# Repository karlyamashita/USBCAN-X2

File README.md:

USBCAN-X2 dual CAN bus analyzer using a STM32G491CE.

The schematic and gerber files are open source.

### Description
I have been working on a [CAN Jammer](https://github.com/karlyamashita/CAN_Jammer_STM32F105RB) project and need a dual CAN bus analyzer that uses 1 STM32 microcontroller. I am finding it difficult to find a vendor that sells a dual CAN bus analyzer that uses an STM32 that is open source and does not read protect the STM32 at RDP level 2. Most vendors that i've contacted are using NXP or a Chinese brand microcontroller. 
<br><br>
Because of the difficulties of finding a dual CAN bus analyzer, I've decided to create this open source project. Since FDCAN is becoming more mainstream, I've decided to use the STM32G491CE with FDCAN controllers which meet the requirements. 

### PCB
The PBC was designed around the USBCAN-2A, matching the USB and screw terminal connector. I am hoping some Chinese manufacturer or someone local will start to manufacture this project to make readily available for purchase. Since the plastic case seems to be a dime a dozen, it will make it easier fo manufacturers to have a completely enclosed product without the need to tool for a new case, if I did create a different size PCB.

`USBCAN-2A`

### Firmware
The FW is being developed and will be open source.

### Software
CAN-X will support the USBCAN-X2 once the Firmware is done.

### Image
This is the 3D image of the USBCAN-X2

`USBCAN-X2`

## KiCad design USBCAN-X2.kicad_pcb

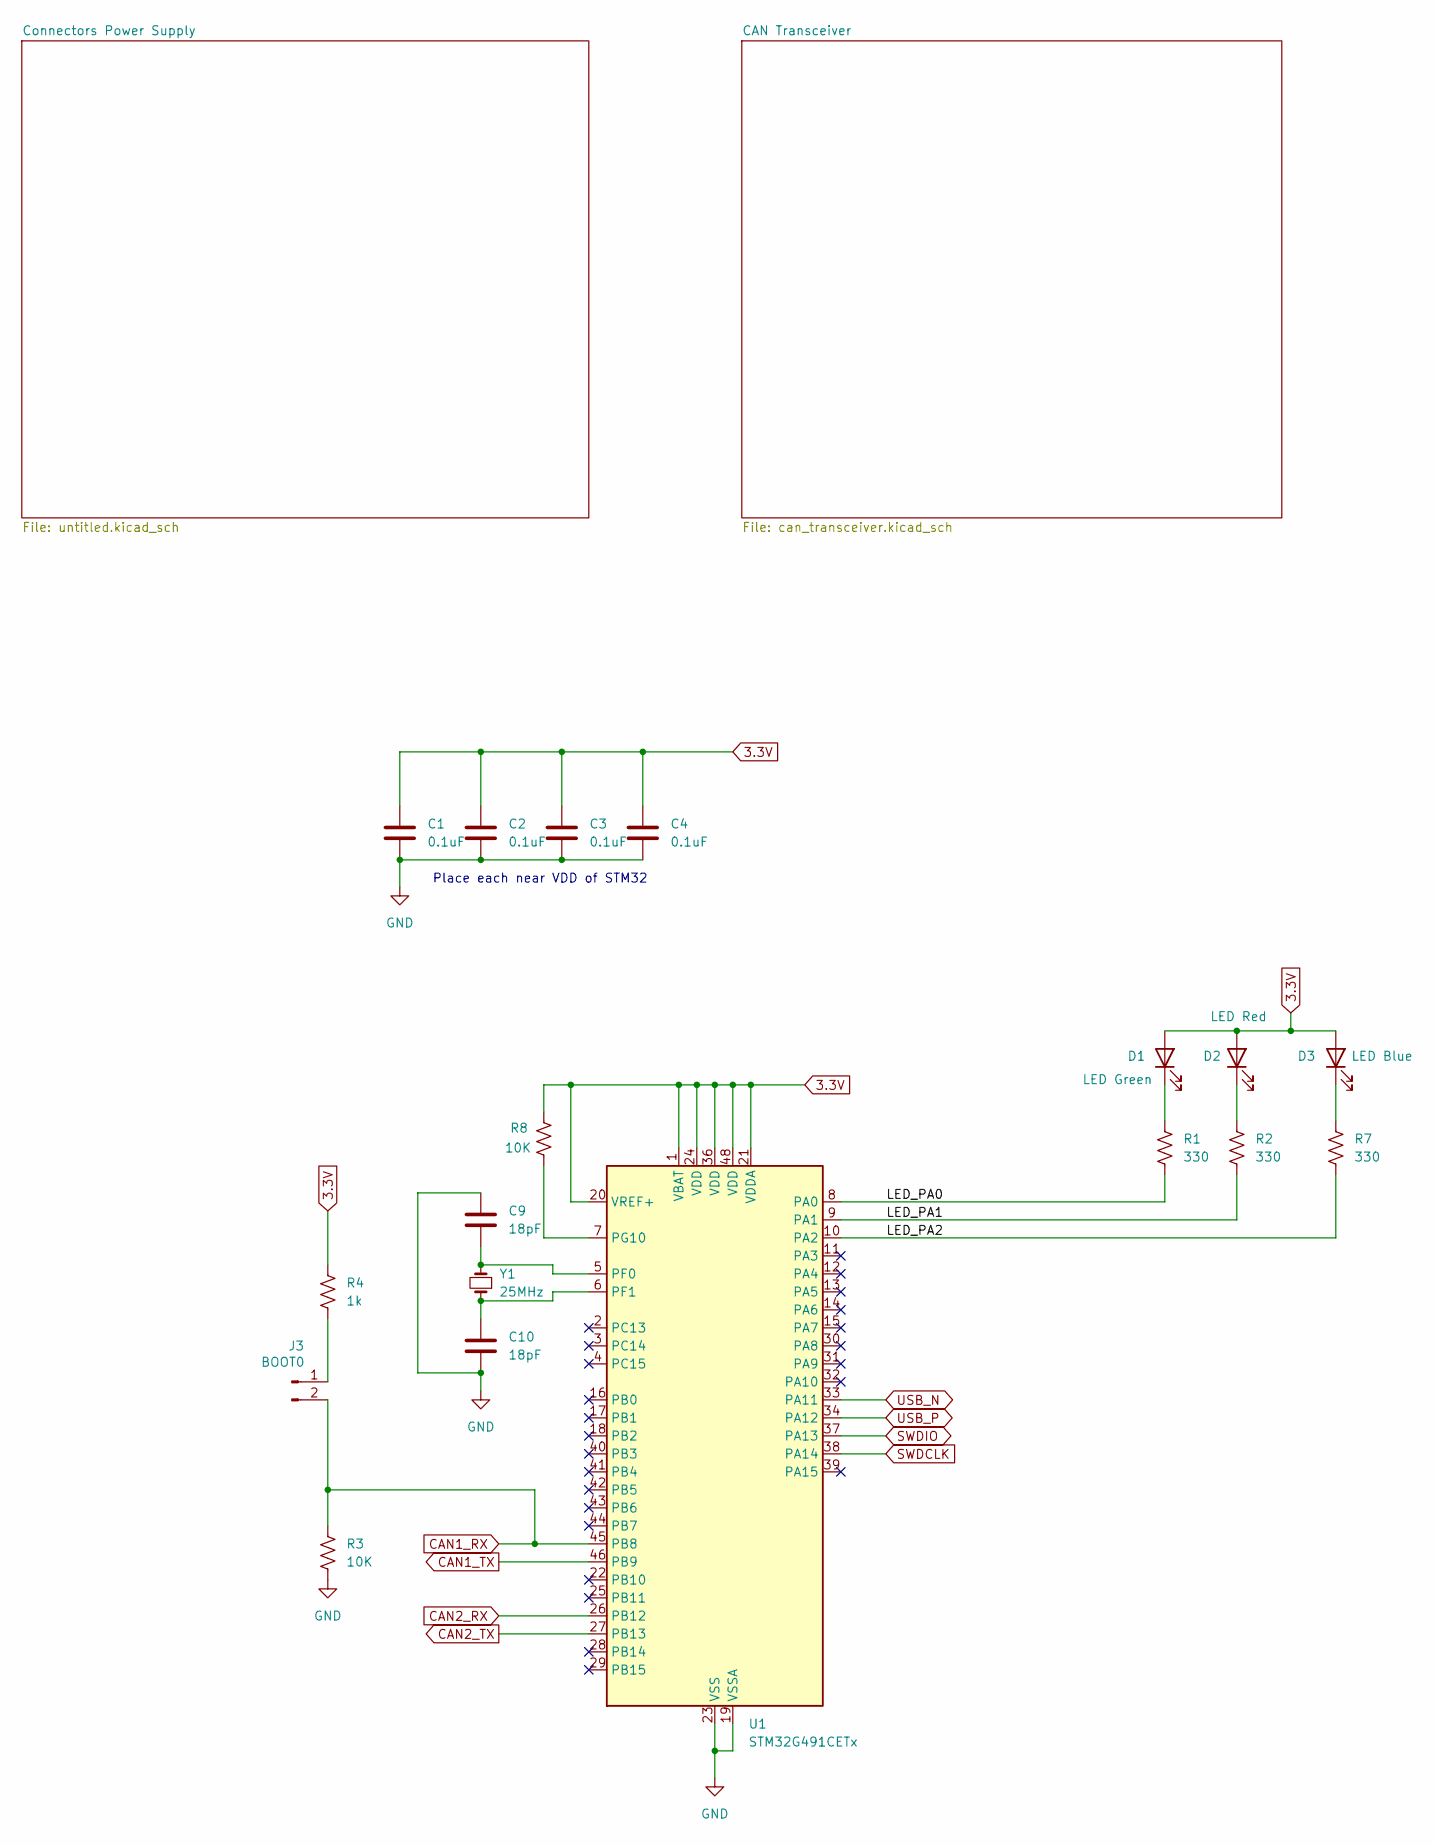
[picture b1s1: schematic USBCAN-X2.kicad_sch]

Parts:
C1, C2, C3, C4: 0.1uF; C_0603_1608Metric; Mouser 603-C0603ZRY5V9BB104
C9, C10: 18pF; C_0603_1608Metric; Mouser 791-RF18N180J500CT
D1: LED Red; LED_0603_1608Metric; Mouser 710-150060RS83000
D2: LED Green; LED_0603_1608Metric; Mouser 710-150060GS83000
D3: LED Blue; LED_0603_1608Metric; Mouser 710-150060BS83000
J3: BOOT0; PinHeader_1x02_P2.54mm_Vertical
R1, R2, R7: 330; R_0603_1608Metric; Mouser 774-73L2R33J
R3, R8: 10K; R_0603_1608Metric; Mouser 603-AC0603JR-7W10KL
R4: 1k; R_0603_1608Metric; Mouser 603-SR0603JR-071KL
U1: STM32G491CETx; LQFP-48_7x7mm_P0.5mm; Mouser 511-STM32G491CET6
Y1: 25MHz; Crystal_SMD_Abracon_ABM7-2Pin_6.0x3.5mm; Mouser 815-ABM725000MHZ4T

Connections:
3.3V: C1.1, C2.1, C3.1, C4.1, D1.2 (A), D2.2 (A), D3.2 (A), R4.1, R8.1, U1.1 (VBAT), U1.20 (VREF+), U1.21 (VDDA), U1.24 (VDD), U1.36 (VDD), U1.48 (VDD); also elsewhere on the board
/LED_PA0: R1.2, U1.8 (PA0)
/LED_PA1: R2.2, U1.9 (PA1)
/LED_PA2: R7.2, U1.10 (PA2)
CAN1_RX: J3.2, R3.1, U1.45 (PB8); also elsewhere on the board
CAN1_TX: U1.46 (PB9); also elsewhere on the board
CAN2_RX: U1.26 (PB12); also elsewhere on the board
CAN2_TX: U1.27 (PB13); also elsewhere on the board
GND: C1.2, C2.2, C3.2, C4.2, C9.1, C10.2, R3.2, U1.19 (VSSA), U1.23 (VSS), U1.35 (VSS), U1.47 (VSS); also elsewhere on the board
unnamed: D1.1 (K), R1.1
unnamed: D2.1 (K), R2.1
unnamed: D3.1 (K), R7.1
unnamed: J3.1, R4.2
unnamed: C9.2, U1.5 (PF0), Y1.2
unnamed: C10.1, U1.6 (PF1), Y1.1
unnamed: R8.2, U1.7 (PG10)
SWDCLK: U1.38 (PA14); also elsewhere on the board
SWDIO: U1.37 (PA13); also elsewhere on the board
USB_N: U1.33 (PA11); also elsewhere on the board
USB_P: U1.34 (PA12); also elsewhere on the board

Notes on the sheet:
Place each near VDD of STM32

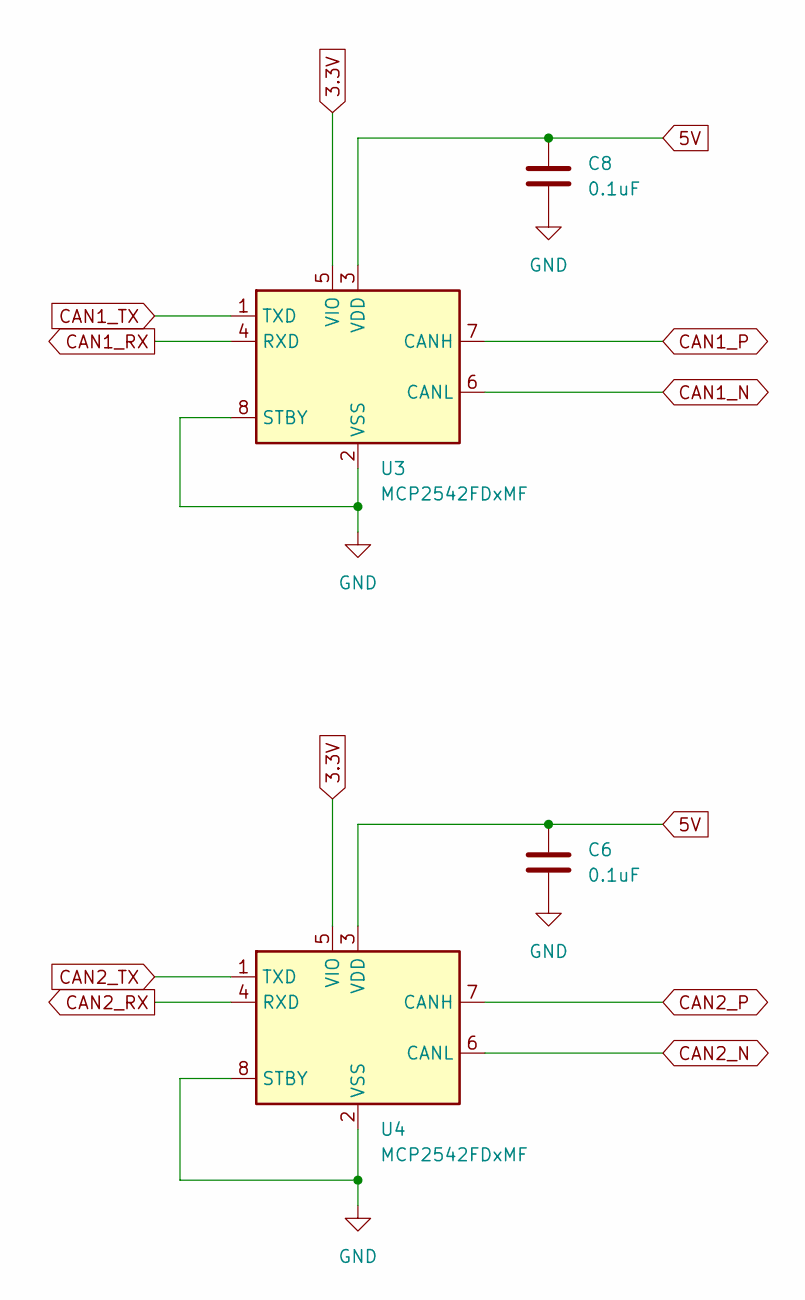
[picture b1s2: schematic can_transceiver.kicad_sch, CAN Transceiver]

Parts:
C6, C8: 0.1uF; C_0603_1608Metric; Mouser 603-C0603ZRY5V9BB104
U3, U4: MCP2542FDxMF; SOIC-8-1EP_3.9x4.9mm_P1.27mm_EP2.29x3mm; Mouser 579-MCP2542FD-E/SN

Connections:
3.3V: U3.5 (VIO), U4.5 (VIO); also elsewhere on the board
5V: C6.1, C8.1, U3.3 (VDD), U4.3 (VDD); also elsewhere on the board
CAN1_N: U3.6 (CANL); also elsewhere on the board
CAN1_P: U3.7 (CANH); also elsewhere on the board
CAN1_RX: U3.4 (RXD); also elsewhere on the board
CAN1_TX: U3.1 (TXD); also elsewhere on the board
CAN2_N: U4.6 (CANL); also elsewhere on the board
CAN2_P: U4.7 (CANH); also elsewhere on the board
CAN2_RX: U4.4 (RXD); also elsewhere on the board
CAN2_TX: U4.1 (TXD); also elsewhere on the board
GND: C6.2, C8.2, U3.2 (VSS), U3.8 (STBY), U3.9 (VSS), U4.2 (VSS), U4.8 (STBY), U4.9 (VSS); also elsewhere on the board

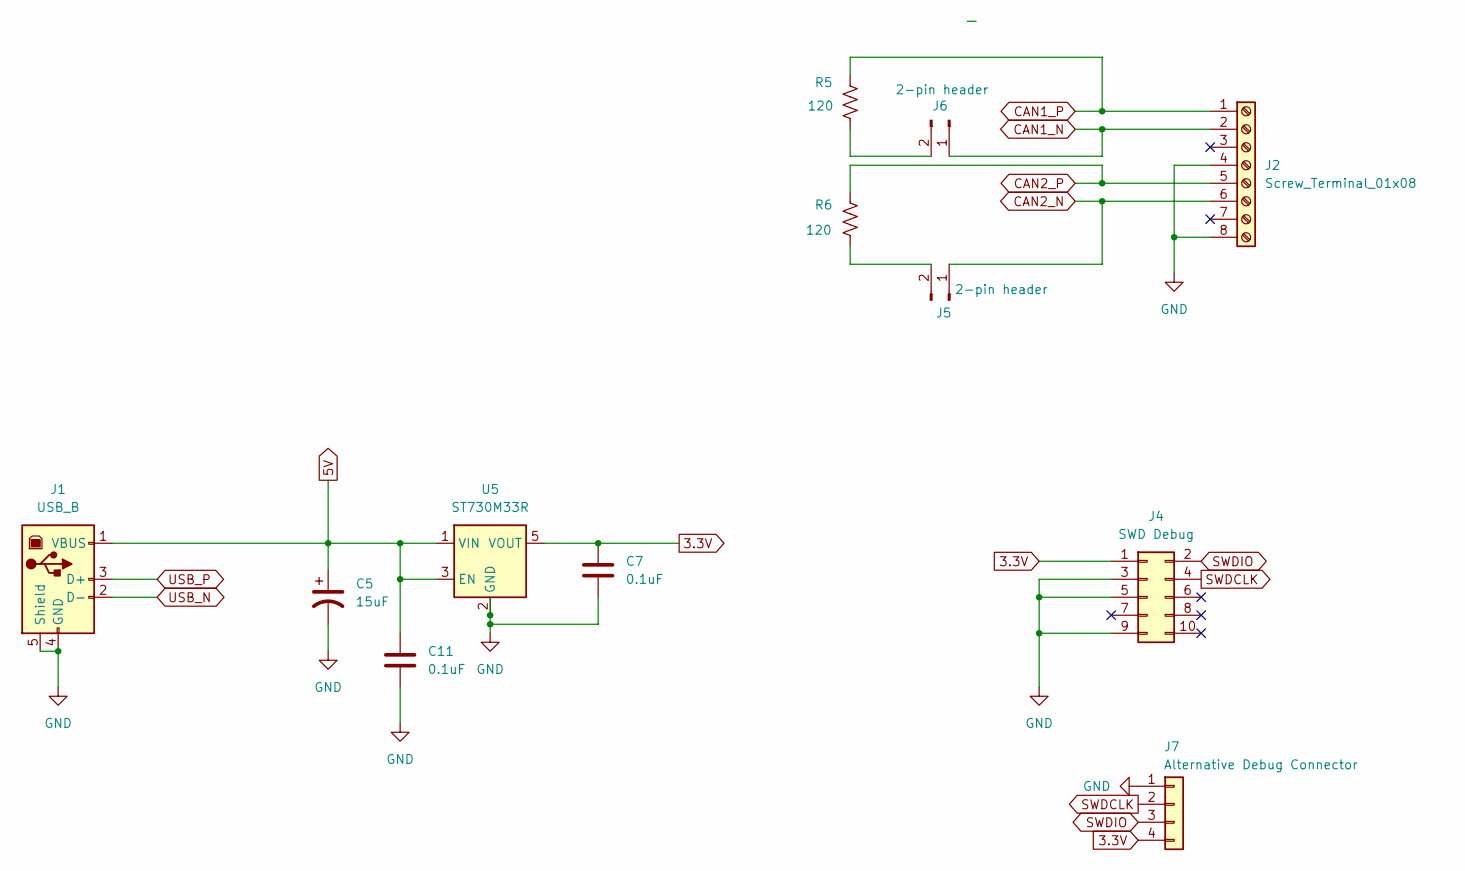
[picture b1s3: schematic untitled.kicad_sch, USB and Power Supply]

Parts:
C5: 15uF; C_Elec_4x5.4; Mouser 667-10SVP15M
C7, C11: 0.1uF; C_0603_1608Metric; Mouser 603-C0603ZRY5V9BB104
J1: USB_B; USB_B_Lumberg_2411_02_Horizontal; Mouser 523-UE27-BC54-100
J2: Screw_Terminal_01x08; Amphenol Anytek OQ0812510000G; Mouser 649-220110-C081A01LF
J4: SWD Debug; CON10_2X5_DUK_FTSH_SAI-M; Mouser 200-FTSH10501LDVKP
J5, J6: 2-pin header; PinHeader_1x02_P2.54mm_Vertical
J7: Alternative Debug Connector; PinHeader_1x04_P2.54mm_Vertical
R5, R6: 120; R_0603_1608Metric; Mouser 603-RC0603FR-13120RL
U5: ST730M33R; SOT-23-5; Mouser ST730M33R

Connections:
3.3V: C7.1, J4.1, J7.4, U5.5 (VOUT); also elsewhere on the board
5V: C5.1, C11.1, J1.1 (VBUS), U5.1 (VIN), U5.3 (EN); also elsewhere on the board
CAN1_N: J2.2, J6.1; also elsewhere on the board
CAN1_P: J2.1, R5.1; also elsewhere on the board
CAN2_N: J2.6, J5.1; also elsewhere on the board
CAN2_P: J2.5, R6.1; also elsewhere on the board
GND: C5.2, C7.2, C11.2, J1.4 (GND), J1.5 (Shield), J2.4, J2.8, J4.3, J4.5, J4.9, J7.1, U5.2 (GND); also elsewhere on the board
unnamed: J5.2, R6.2
unnamed: J6.2, R5.2
SWDCLK: J4.4, J7.2; also elsewhere on the board
SWDIO: J4.2, J7.3; also elsewhere on the board
USB_N: J1.2 (D-); also elsewhere on the board
USB_P: J1.3 (D+); also elsewhere on the board

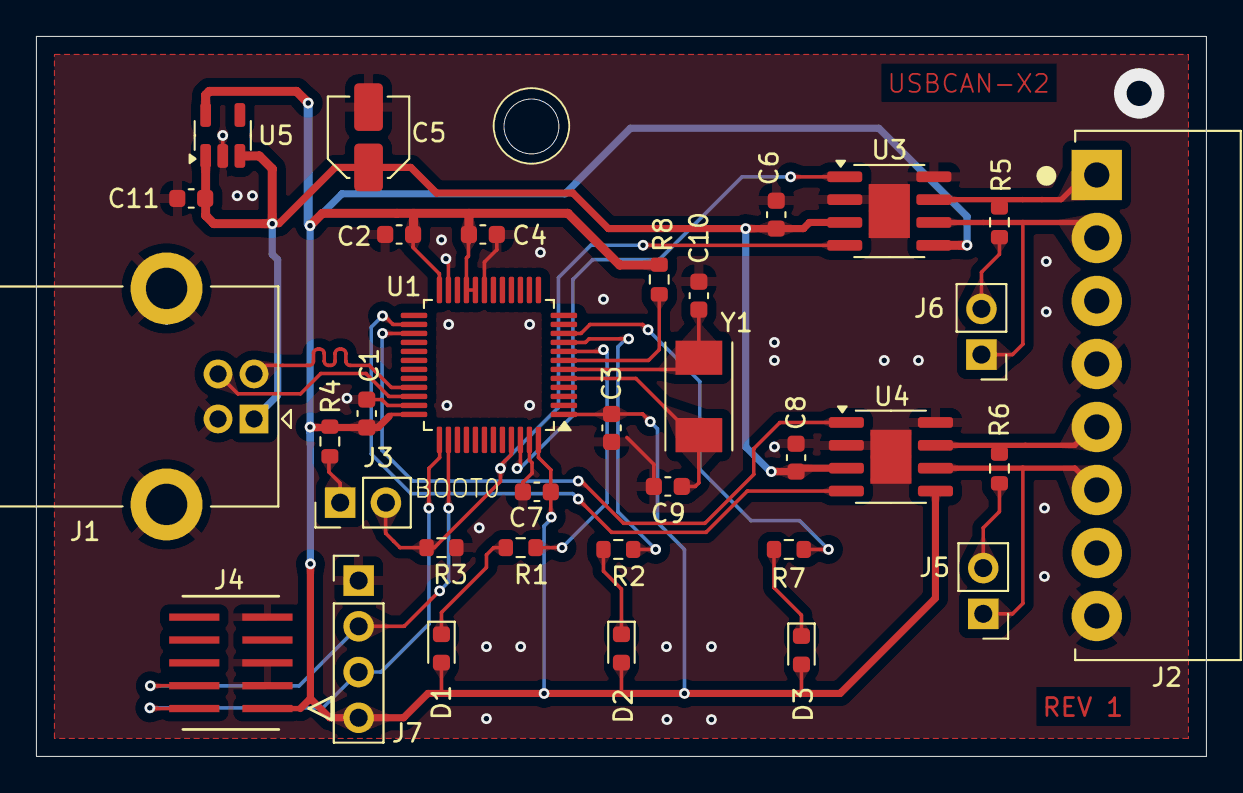
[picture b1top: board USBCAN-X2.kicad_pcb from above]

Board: 2 copper layers, 65.0 x 40.0 mm, 34 parts (0 on the bottom side), 27 nets.

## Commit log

2025-09-18 Init commit. Board outline is a mockup until I get actual dimensions.
2025-09-19 Created PDF's
2025-09-19 Moved CAN transceiver and jumper pins. Rerouted tracks. Added 3D models to 3D folder as they are linked and not embedded.
2025-09-19 Added an alternative 4-pin debug header
2025-09-21 Add pull-up to NRST
2025-09-22 Clean some tracks up.

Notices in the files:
USBCAN-X2.kicad_pcb:
Copyright 2025 Karl Yamashita
